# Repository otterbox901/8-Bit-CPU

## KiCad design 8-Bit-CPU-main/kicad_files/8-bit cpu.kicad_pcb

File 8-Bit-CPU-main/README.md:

# 8-Bit CPU

A CPU built from ~97 individual 74HC-series logic ICs. Custom instruction set, microcoded control unit, and a from-scratch ALU with flag logic, laid out on a 4-layer PCB.

## Status: In progress

- [x] Instruction set architecture (11 instructions, custom encoding)
- [x] ALU design — adder/subtractor, bitwise AND/OR, Z/C/N flag generation
- [x] Register file (4 general-purpose registers) and microcoded control-ROM addressing scheme
- [x] PCB component placement — 97 ICs, board outline drawn (173.5 mm × 115.5 mm, 4-layer)
- [x] Microcode ROM generator — Python script producing control-ROM contents from the ISA/microcode design, checked against the control-unit addressing scheme
- [x] Emulator — Python simulator + assembler that executes `microcode_table.csv` directly, with the full ISA exercised by a bundled test program
- [x] Control unit — the schematic's control-ROM addressing, register-file/ALU
      enable logic, and memory control signals are now actually wired
- [x] PCB routing — fully autorouted (4-layer, 755 nets, 0 DRC errors)
- [ ] Power input connector + regulator (not yet designed — see Known Issues)
- [ ] HLT (clock/sequencer halt) — control-ROM signal exists but isn't wired
      to anything yet
- [ ] Burn control ROM onto physical EEPROMs and hardware bring-up

## Overview

| | |
|---|---|
| Data path | 8-bit |
| Registers | 4 general-purpose (R0–R3), plus PC, MAR, IR, and internal ALU staging registers |
| Control unit | Microcoded — control ROM addressed by opcode, execution step, and ALU status flags (no hardwired branch/decision logic) |
| ALU | Add, subtract (two's complement), AND, OR — with Zero, Carry, and Negative flags |
| Memory | Harvard-style — separate address space for program storage (EEPROM) and data storage (SRAM) |
| Clock target | 1–4 MHz |
| Logic family | 74HC/74LS discrete logic |
| IC count | ~97 |
| Board | 4-layer, 1.6 mm, 173.5 mm × 115.5 mm |

## Instruction Set

| Opcode | Mnemonic | Format | Operation |
|---|---|---|---|
| `0000` | `NOP` | — | No operation |
| `0001` | `LOAD Rd, addr` | Address (3 bytes) | Rd ← MEM[addr] |
| `0010` | `STORE Rd, addr` | Address (3 bytes) | MEM[addr] ← Rd |
| `0011` | `ADD Rd, Rs` | Reg-reg (1 byte) | Rd ← Rd + Rs |
| `0100` | `SUB Rd, Rs` | Reg-reg (1 byte) | Rd ← Rd − Rs |
| `0101` | `JMP addr` | Address (3 bytes) | PC ← addr |
| `0110` | `JZ addr` | Address (3 bytes) | PC ← addr if Zero flag set |
| `0111` | `JC addr` | Address (3 bytes) | PC ← addr if Carry flag set |
| `1000` | `MOV Rd, Rs` | Reg-reg (1 byte) | Rd ← Rs |
| `1001` | `AND Rd, Rs` | Reg-reg (1 byte) | Rd ← Rd AND Rs |
| `1010` | `OR Rd, Rs` | Reg-reg (1 byte) | Rd ← Rd OR Rs |
| `1111` | `HLT` | — | Stop the clock |

Opcodes `1011`–`1110` are reserved for future extension (e.g. a stack pointer with `CALL`/`RET`, or additional ALU operations). Currently they fetch and decode as a no-op.

Instructions are encoded as either one byte (reg-reg) or three bytes (address):

| Format | Byte 0 | Byte 1 | Byte 2 |
|---|---|---|---|
| Reg-reg | `[opcode:4][Rd:2][Rs:2]` | — | — |
| Address | `[opcode:4][Rd:2][--:2]` | addr low | addr high |

The 3-bit step counter cycles 0–7 (wrapping); step 0 is always the fetch (`IROM_OUT` + `IR_IN` + `PC_INC`), steps 1–3 execute the operand/operation, and any trailing steps are no-ops. Conditional jumps are resolved entirely by the control ROM's addressing (the flag bits are part of the ROM address), with no separate comparator logic needed.

## Control ROM

The control ROM is generated rather than hand-populated. A Python script (`microcode_rom_gen.py`) walks every `(opcode, step, Z, C)` combination — a 9-bit, 512-word address space, and derives the 20-bit control word for each from the microcode step tables for each instruction. The control word is split across three 28C256 EEPROMs (8 + 8 + 4 bits), and the script emits both a human-readable CSV (`microcode_table.csv`) and three raw 32 KB binary chip images (`rom1.bin`, `rom2.bin`, `rom3.bin`) ready to burn, with unused upper addresses zero-padded to an all-signals-off state.

## Emulator

`emulator.py` is a cycle-accurate Python model of the CPU driven entirely by the generated control ROM. It arbitrates the 8-bit bus, latches registers and flags per the microcode control signals, and assembles + runs programs, so it can be used to develop and verify software before the hardware comes up.

### Usage

```bash
# Generate the control ROM table first (run from ROM/)
python3 microcode_rom_gen.py

# Run the full instruction-set test program (7/7 checks pass)
python3 emulator.py test_program.asm

# Run the bundled default test (no file argument)
python3 emulator.py

# Per-micro-step trace of bus, registers, and control signals
python3 emulator.py test_program.asm --trace-micro

# Quiet mode — suppress trace, show results only
python3 emulator.py -q test_program.asm
```

The built-in two-pass assembler understands the instruction mnemonics, labels, hex/decimal numbers, `.byte` (program ROM data) and `.ram addr, val` (pre-loads the data SRAM) directives. `test_program.asm` exercises every instruction — LOAD, STORE, ADD, SUB, AND, OR, MOV, NOP, JMP, JZ, JC, HLT — and auto-verifies the resulting data RAM contents against expected values.

## Repo Contents

```
8-Bit-CPU/
├── 8-bit cpu.kicad_sch     KiCad schematic (single flat sheet)
├── 8-bit cpu.kicad_pcb     KiCad PCB layout (routed, 0 DRC errors)
├── microcode_rom_gen.py    Control ROM generator (opcode/step/flags → EEPROM images)
├── emulator.py             Microcode-driven CPU emulator + assembler
├── test_program.asm        Full instruction-set test for the emulator
└── README.md
```

## Known Issues

- **No power input connector or regulator.** All 63 live ICs now share a
  single, correctly-named `+5V` net, but nothing in the schematic actually
  sources it — there's no barrel jack/header and no regulator IC modeled.
  This needs to be designed and added before the board can be powered.
- **HLT isn't wired to anything.** The control ROM correctly asserts the
  `HLT` signal per the microcode, but no hardware currently reads it (no
  clock-gating or sequencer-halt logic exists). Without it, a running CPU
  won't literally stop on `HLT` — it'll keep re-fetching the same
  instruction harmlessly forever rather than actually halting.
- **Cosmetic-only DRC/ERC output remains**: ~55 silkscreen text/outline
  overlaps among tightly-packed passives, and footprint-library-name
  mismatches (PCB footprints reference a `fasteda` library not present in
  every environment — the footprint geometry is embedded in the file
  regardless, so this doesn't affect fabrication).
- None of this has been verified against real hardware yet — see Roadmap.

## Roadmap

1. Design and add a power input connector + regulator
2. Wire HLT to a sequencer-halt/clock-gate
3. Burn the generated control ROM contents onto the EEPROMs
4. Bring-up and testing
5. Print and test on physical hardware

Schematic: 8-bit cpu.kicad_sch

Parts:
C1, C2, C3, C4, C5, C6, C7, C8, C9, C10, C11, C12, C13, C14, C15, C16, C17, C18, C19, C20, C21, C22, C23, C24, C25, C26, C27, C28, C29, C30, C31, C32: 100nF; C0805
R1: 10k; R0805
SW1: HX 3X4X2-2P-1.6N TACTILE SWITCH; KEY-SMD_L4.0-W3.0-LS4.9-1; MPN HX 3x4x2-2P-1.6N TACTILE SWITCH; LCSC C49234124
U1, U2, U3, U4, U32, U33, U34, U35, U44, U45, U46, U47, U48, U49, U50, U51, U55, U56: 74HC173D,653; SOP-16_L10.0-W3.9-P1.27-LS6.0-BL; MPN 74HC173D,653; LCSC C546652
U5, U6: CD74HC283M96; SOIC-16_L9.9-W3.9-P1.27-LS6.0-BL; MPN CD74HC283M96; LCSC C543032; not fitted
U7, U8: SN74HC86DR; SOIC-14_L8.7-W3.9-P1.27-LS6.0-BL; MPN SN74HC86DR; LCSC C6763
U9, U10, U11, U12, U38, U39, U40, U41: 74HC153D,653; SOIC-16_L9.9-W3.9-P1.27-LS6.0-BL; MPN 74HC153D,653; LCSC C53334
U13: 74HC245D,653; SOIC-20_L13.0-W7.6-P1.27-LS10.3-BL; MPN 74HC245D,653; LCSC C5625; not fitted
U14, U15: 74HC08D,653; SOIC-14_L8.7-W3.9-P1.27-LS6.0-BL; MPN 74HC08D,653; LCSC C5593
U16, U17, U18, U19: 74HC32D,653; SOIC-14_L8.7-W3.9-P1.27-LS6.0-BL; MPN 74HC32D,653; LCSC C5632
U20: 74HC04D,653; SOIC-14_L8.7-W3.9-P1.27-LS6.0-BL; MPN 74HC04D,653; LCSC C5590
U21: 74HC173D,653; SOP-16_L10.0-W3.9-P1.27-LS6.0-BL; MPN 74HC173D,653; LCSC C546652; not fitted
U22, U23, U24: AT28C256-15SU; SOIC-28_L17.9-W7.6-P1.27-LS10.4-BL; MPN AT28C256-15SU; LCSC C1349121; not fitted
U25, U52, U53, U54: SN74HC161DR; SOIC-16_L9.9-W3.9-P1.27-LS6.0-BL; MPN SN74HC161DR; LCSC C6824
U26, U27, U28, U29, U30: SN74HC161DR; SOIC-16_L9.9-W3.9-P1.27-LS6.0-BL; MPN SN74HC161DR; LCSC C6824; not fitted
U31: AT28C64B-15PU; DIP-28_L37.0-W13.8-P2.54-LS15.8-BL; MPN AT28C64B-15PU; LCSC C41982; not fitted
U36, U37: CD74HC283M96; SOIC-16_L9.9-W3.9-P1.27-LS6.0-BL; MPN CD74HC283M96; LCSC C543032
U42: 74HC245D,653; SOIC-20_L13.0-W7.6-P1.27-LS10.3-BL; MPN 74HC245D,653; LCSC C5625
U43: 74HC139D,653; SOIC-16_L9.9-W3.9-P1.27-LS6.0-BL; MPN 74HC139D,653; LCSC C5603
U57, U58, U59: AT28C256-15SU; SOIC-28_L17.9-W7.6-P1.27-LS10.4-BL; MPN AT28C256-15SU; LCSC C1349121
U60: AT28C64B-15PU; DIP-28_L37.0-W13.8-P2.54-LS15.8-BL; MPN AT28C64B-15PU; LCSC C41982
U61: HM6116LP-4; DIP-24_W15.24mm_P2.54mm; MPN HM6116LP-4
U62: OT70501MJBA4SL; OSC-SMD_4P-L7.0-W5.0-BL-2; MPN OT70501MJBA4SL; LCSC C2831414
U63: SN74HC14DR; SOIC-14_L8.7-W3.9-P1.27-LS6.0-BL; MPN SN74HC14DR; LCSC C6820

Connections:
+5V: C1.1, C2.1, C3.1, C4.1, C5.1, C6.1, C7.1, C8.1, C9.1, C10.1, C11.1, C12.1, C13.1, C14.1, C15.1, C16.1, C17.1, C18.1, C19.1, C20.1, C21.1, C22.1, C23.1, C24.1, C25.1, C26.1, C27.1, C28.1, C29.1, C30.1, C31.1, C32.1, R1.1, U1.16 (VCC), U2.16 (VCC), U3.16 (VCC), U4.16 (VCC), U5.16 (VCC), U6.16 (VCC), U7.14 (VCC), U8.14 (VCC), U9.16 (VCC), U10.6 (1I0), U10.10 (2I0), U10.16 (VCC), U11.6 (1I0), U11.10 (2I0), U11.16 (VCC), U12.6 (1I0), U12.10 (2I0), U12.16 (VCC), U13.20 (VCC), U14.14 (VCC), U15.14 (VCC), U16.14 (VCC), U17.14 (VCC), U18.14 (VCC), U19.14 (VCC), U20.14 (VCC), U21.16 (VCC), U22.28 (VCC), U23.27 (~WE), U23.28 (VCC), U24.28 (VCC), U25.7 (ENP), U25.9 (~LOAD), U25.10 (ENT), U25.16 (VCC), U26.16 (VCC), U27.16 (VCC), U28.16 (VCC), U29.16 (VCC), U30.16 (VCC), U31.28 (VCC), U32.16 (VCC), U33.16 (VCC), U34.16 (VCC), U35.16 (VCC), U36.16 (VCC), U37.16 (VCC), U38.16 (VCC), U39.16 (VCC), U40.16 (VCC), U41.16 (VCC), U42.20 (VCC), U43.16 (VCC), U44.16 (VCC), U45.16 (VCC), U46.16 (VCC), U47.16 (VCC), U48.16 (VCC), U49.16 (VCC), U50.16 (VCC), U51.16 (VCC), U52.16 (VCC), U53.16 (VCC), U54.16 (VCC), U55.16 (VCC), U56.16 (VCC), U57.27 (~WE), U57.28 (VCC), U58.27 (~WE), U58.28 (VCC), U59.27 (~WE), U59.28 (VCC), U60.27 (~WE), U60.28 (VCC), U61.24 (VCC), U62.1 (Tri-state), U62.4 (VDD), U63.14 (VCC)
A0: U23.10 (A0), U31.10 (A0)
A1: U23.9 (A1), U31.9 (A1)
A2: U23.8 (A2), U31.8 (A2)
A3: U23.7 (A3), U31.7 (A3)
A4: U23.6 (A4), U31.6 (A4)
A5: U23.5 (A5), U31.5 (A5)
A6: U23.4 (A6), U31.4 (A6)
A7: U23.3 (A7), U31.3 (A7)
A8: U23.25 (A8), U31.25 (A8)
A9: U23.24 (A9), U31.24 (A9)
A10: U23.21 (A10), U31.21 (A10)
A11: U23.23 (A11), U31.23 (A11)
A12: U23.2 (A12), U31.2 (A12)
A13_ADDR: U23.26 (A13)
A14: U23.1 (A14)
ALU_A0: U14.1 (1A), U16.1 (1A), U32.3 (Q0), U36.5 (A0)
ALU_A0_2: U5.5 (A0)
ALU_A1: U14.4 (2A), U16.4 (2A), U32.4 (Q1), U36.3 (A1)
ALU_A1_2: U5.3 (A1)
ALU_A2: U14.9 (3A), U16.9 (3A), U32.5 (Q2), U36.14 (A2)
ALU_A2_2: U5.14 (A2)
ALU_A3: U14.12 (4A), U16.12 (4A), U32.6 (Q3), U36.12 (A3)
ALU_A3_2: U5.12 (A3)
ALU_A4: U15.1 (1A), U17.1 (1A), U34.3 (Q0), U37.5 (A0)
ALU_A4_2: U6.5 (A0)
ALU_A5: U15.4 (2A), U17.4 (2A), U34.4 (Q1), U37.14 (A2)
ALU_A5_2: U6.14 (A2)
ALU_A6: U15.9 (3A), U17.9 (3A), U34.5 (Q2), U37.3 (A1)
ALU_A6_2: U6.3 (A1)
ALU_A7: U15.12 (4A), U17.12 (4A), U34.6 (Q3), U37.12 (A3)
ALU_A7_2: U6.12 (A3)
ALU_AND0: U14.3 (1Y), U38.5 (1I1)
ALU_AND1: U14.6 (2Y), U38.11 (2I1)
ALU_AND2: U14.8 (3Y), U39.5 (1I1)
ALU_AND3: U14.11 (4Y), U39.11 (2I1)
ALU_AND4: U15.3 (1Y), U40.5 (1I1)
ALU_AND5: U15.6 (2Y), U40.11 (2I1)
ALU_AND6: U15.8 (3Y), U41.5 (1I1)
ALU_AND7: U15.11 (4Y), U41.11 (2I1)
ALU_B0: U7.3 (1Y), U14.2 (1B), U16.2 (1B), U36.6 (B0), U38.3 (1I3)
ALU_B0_2: U5.6 (B0)
ALU_B1: U7.6 (2Y), U14.5 (2B), U16.5 (2B), U36.2 (B1), U38.13 (2I3)
ALU_B1_2: U5.2 (B1)
ALU_B2: U7.8 (3Y), U14.10 (3B), U16.10 (3B), U36.15 (B2), U39.3 (1I3)
ALU_B2_2: U5.15 (B2)
ALU_B3: U7.11 (4Y), U14.13 (4B), U16.13 (4B), U36.11 (B3), U39.13 (2I3)
ALU_B3_2: U5.11 (B3)
ALU_B4: U8.3 (1Y), U15.2 (1B), U17.2 (1B), U37.6 (B0), U40.3 (1I3)
ALU_B4_2: U6.6 (B0)
ALU_B5: U8.6 (2Y), U15.5 (2B), U17.5 (2B), U37.15 (B2), U40.13 (2I3)
ALU_B5_2: U6.15 (B2)
ALU_B6: U8.8 (3Y), U15.10 (3B), U17.10 (3B), U37.2 (B1), U41.3 (1I3)
ALU_B6_2: U6.2 (B1)
ALU_B7: U8.11 (4Y), U15.13 (4B), U17.13 (4B), U37.11 (B3), U41.13 (2I3)
ALU_B7_2: U6.11 (B3)
ALU_B_RAW0: U7.1 (1A), U33.3 (Q0)
ALU_B_RAW1: U7.4 (2A), U33.4 (Q1)
ALU_B_RAW2: U7.9 (3A), U33.5 (Q2)
ALU_B_RAW3: U7.12 (4A), U33.6 (Q3)
ALU_B_RAW4: U8.1 (1A), U35.3 (Q0)
ALU_B_RAW5: U8.4 (2A), U35.4 (Q1)
ALU_B_RAW6: U8.9 (3A), U35.5 (Q2)
ALU_B_RAW7: U8.12 (4A), U35.6 (Q3)
ALU_CARRY_MID: U36.9 (COUT), U37.7 (CIN)
ALU_MUX_OUT0: U18.1 (1A), U38.7 (1Y), U42.18 (B0)
ALU_MUX_OUT1: U18.2 (1B), U38.9 (2Y), U42.17 (B1)
ALU_MUX_OUT2: U18.4 (2A), U39.7 (1Y), U42.16 (B2)
ALU_MUX_OUT3: U18.5 (2B), U39.9 (2Y), U42.15 (B3)
ALU_MUX_OUT4: U18.9 (3A), U40.7 (1Y), U42.14 (B4)
ALU_MUX_OUT5: U18.10 (3B), U40.9 (2Y), U42.13 (B5)
ALU_MUX_OUT6: U18.12 (4A), U41.7 (1Y), U42.12 (B6)
ALU_MUX_OUT7: U18.13 (4B), U41.9 (2Y), U42.11 (B7)
ALU_OR0: U16.3 (1Y), U38.4 (1I2)
ALU_OR1: U16.6 (2Y), U38.12 (2I2)
ALU_OR2: U16.8 (3Y), U39.4 (1I2)
ALU_OR3: U16.11 (4Y), U39.12 (2I2)
ALU_OR4: U17.3 (1Y), U40.4 (1I2)
ALU_OR5: U17.6 (2Y), U40.12 (2I2)
ALU_OR6: U17.8 (3Y), U41.4 (1I2)
ALU_OR7: U17.11 (4Y), U41.12 (2I2)
ALU_S0: U36.4 (S0), U38.6 (1I0)
ALU_S1: U36.1 (S1), U38.10 (2I0)
ALU_S2: U36.13 (S2), U39.6 (1I0)
ALU_S3: U36.10 (S3), U39.10 (2I0)
ALU_S4: U37.4 (S0), U40.6 (1I0)
ALU_S5: U37.1 (S1), U40.10 (2I0)
ALU_S6: U37.13 (S2), U41.6 (1I0)
ALU_S7: U37.10 (S3), U41.10 (2I0)
ALU_SEL0: U38.14 (S0), U39.14 (S0), U40.14 (S0), U41.14 (S0), U58.17 (I/O5)
ALU_SEL1: U38.2 (S1), U39.2 (S1), U40.2 (S1), U41.2 (S1), U58.18 (I/O6)
A_IN: U32.9 (#E1), U32.10 (#E2), U34.9 (#E1), U34.10 (#E2), U58.15 (I/O3)
C: U4.4 (Q1), U57.10 (A0), U58.10 (A0), U59.10 (A0)
CIN: U5.9 (COUT), U6.7 (CIN)
CLK: U1.7 (CP), U2.7 (CP), U3.7 (CP), U4.7 (CP), U25.2 (CLK), U32.7 (CP), U33.7 (CP), U34.7 (CP), U35.7 (CP), U44.7 (CP), U45.7 (CP), U46.7 (CP), U47.7 (CP), U48.7 (CP), U49.7 (CP), U50.7 (CP), U51.7 (CP), U52.2 (CLK), U53.2 (CLK), U54.2 (CLK), U55.7 (CP), U56.7 (CP), U62.3 (OUTPUT)
CLK_2: U21.7 (CP), U26.2 (CLK), U27.2 (CLK), U28.2 (CLK), U29.2 (CLK), U30.2 (CLK)
C_COMPUTED: U4.13 (D1), U37.9 (COUT)
D0: U23.11 (I/O0), U31.11 (IO0)
D1: U23.12 (I/O1), U31.12 (IO1)
D2: U23.13 (I/O2), U31.13 (IO2)
D3: U23.15 (I/O3), U31.15 (IO3)
D4: U23.16 (I/O4), U31.16 (IO4), U59.16 (I/O4)
D5: U23.17 (I/O5), U31.17 (IO5), U59.17 (I/O5)
D6: U23.18 (I/O6), U31.18 (IO6), U59.18 (I/O6)
D7: U23.19 (I/O7), U31.19 (IO7), U59.19 (I/O7)
DBUS0: U1.14 (D0), U3.14 (D0), U32.14 (D0), U33.14 (D0), U42.2 (A0), U44.3 (Q0), U44.14 (D0), U46.3 (Q0), U46.14 (D0), U48.3 (Q0), U48.14 (D0), U50.3 (Q0), U50.14 (D0), U55.14 (D0), U60.11 (IO0), U61.9 (I/O0)
DBUS0_2: U13.2 (A0), U21.14 (D0)
DBUS1: U1.13 (D1), U3.13 (D1), U32.13 (D1), U33.13 (D1), U42.3 (A1), U44.4 (Q1), U44.13 (D1), U46.4 (Q1), U46.13 (D1), U48.4 (Q1), U48.13 (D1), U50.4 (Q1), U50.13 (D1), U55.13 (D1), U60.12 (IO1), U61.10 (I/O1)
DBUS1_2: U13.3 (A1), U21.13 (D1)
DBUS2: U1.12 (D2), U3.12 (D2), U32.12 (D2), U33.12 (D2), U42.4 (A2), U44.5 (Q2), U44.12 (D2), U46.5 (Q2), U46.12 (D2), U48.5 (Q2), U48.12 (D2), U50.5 (Q2), U50.12 (D2), U55.12 (D2), U60.13 (IO2), U61.11 (I/O2)
DBUS2_2: U13.4 (A2), U21.12 (D2)
DBUS3: U1.11 (D3), U3.11 (D3), U32.11 (D3), U33.11 (D3), U42.5 (A3), U44.6 (Q3), U44.11 (D3), U46.6 (Q3), U46.11 (D3), U48.6 (Q3), U48.11 (D3), U50.6 (Q3), U50.11 (D3), U55.11 (D3), U60.15 (IO3), U61.13 (I/O3)
DBUS3_2: U13.5 (A3), U21.11 (D3)
DBUS4: U2.14 (D0), U34.14 (D0), U35.14 (D0), U42.6 (A4), U45.3 (Q0), U45.14 (D0), U47.3 (Q0), U47.14 (D0), U49.3 (Q0), U49.14 (D0), U51.3 (Q0), U51.14 (D0), U56.14 (D0), U60.16 (IO4), U61.14 (I/O4)
DBUS5: U2.13 (D1), U34.13 (D1), U35.13 (D1), U42.7 (A5), U45.4 (Q1), U45.13 (D1), U47.4 (Q1), U47.13 (D1), U49.4 (Q1), U49.13 (D1), U51.4 (Q1), U51.13 (D1), U56.13 (D1), U60.17 (IO5), U61.15 (I/O5)
DBUS6: U2.12 (D2), U34.12 (D2), U35.12 (D2), U42.8 (A6), U45.5 (Q2), U45.12 (D2), U47.5 (Q2), U47.12 (D2), U49.5 (Q2), U49.12 (D2), U51.5 (Q2), U51.12 (D2), U56.12 (D2), U60.18 (IO6), U61.16 (I/O6)
DBUS7: U2.11 (D3), U34.11 (D3), U35.11 (D3), U42.9 (A7), U45.6 (Q3), U45.11 (D3), U47.6 (Q3), U47.11 (D3), U49.6 (Q3), U49.11 (D3), U51.6 (Q3), U51.11 (D3), U56.11 (D3), U60.19 (IO7), U61.17 (I/O7)
EO: U12.14 (S0), U59.11 (I/O0)
EO_N: U12.7 (1Y), U12.9 (2Y), U42.19 (~OE)
FI_C: U19.13 (4B), U59.13 (I/O2)
FI_LATCH_N: U4.9 (#E1), U4.10 (#E2), U11.7 (1Y), U11.9 (2Y)
FI_OR: U11.14 (S0), U19.11 (4Y)
FI_ZN: U19.12 (4A), U59.12 (I/O1)
HLT: U59.15 (I/O3)
IROM_OUT: U20.1 (1A), U57.11 (I/O0)
IROM_OUT_N: U20.2 (1Y), U60.22 (~OE)
IR_IN: U55.9 (#E1), U55.10 (#E2), U56.9 (#E1), U56.10 (#E2), U57.15 (I/O3)
IR_RD0: U9.6 (1I0), U55.5 (Q2)
IR_RD1: U9.10 (2I0), U55.6 (Q3)
IR_RS0: U9.5 (1I1), U55.3 (Q0)
IR_RS1: U9.11 (2I1), U55.4 (Q1)
MARH0: U3.3 (Q0), U54.3 (A), U61.23 (A8)
MARH1: U3.4 (Q1), U54.4 (B), U61.22 (A9)
MARH2: U3.5 (Q2), U54.5 (C), U61.19 (A10)
MARH3: U3.6 (Q3), U54.6 (D)
MARL0: U1.3 (Q0), U52.3 (A), U61.8 (A0)
MARL1: U1.4 (Q1), U52.4 (B), U61.7 (A1)
MARL2: U1.5 (Q2), U52.5 (C), U61.6 (A2)
MARL3: U1.6 (Q3), U52.6 (D), U61.5 (A3)
MARL4: U2.3 (Q0), U53.3 (A), U61.4 (A4)
MARL5: U2.4 (Q1), U53.4 (B), U61.3 (A5)
MARL6: U2.5 (Q2), U53.5 (C), U61.2 (A6)
MARL7: U2.6 (Q3), U53.6 (D), U61.1 (A7)
MAR_HIGH_IN: U3.9 (#E1), U3.10 (#E2), U57.17 (I/O5)
MAR_LOW_IN: U1.9 (#E1), U1.10 (#E2), U2.9 (#E1), U2.10 (#E2), U57.16 (I/O4)
unnamed: SW1.1, U63.1 (1A)
OE: U23.22 (~OE)
OPCODE0: U56.3 (Q0), U57.5 (A5), U58.5 (A5), U59.5 (A5)
OPCODE1: U56.4 (Q1), U57.4 (A6), U58.4 (A6), U59.4 (A6)
OPCODE2: U56.5 (Q2), U57.3 (A7), U58.3 (A7), U59.3 (A7)
OPCODE3: U56.6 (Q3), U57.25 (A8), U58.25 (A8), U59.25 (A8)
PC0: U52.14 (QA), U60.10 (A0)
PC1: U52.13 (QB), U60.9 (A1)
PC2: U52.12 (QC), U60.8 (A2)
PC3: U52.11 (QD), U60.7 (A3)
PC4: U53.14 (QA), U60.6 (A4)
PC5: U53.13 (QB), U60.5 (A5)
PC6: U53.12 (QC), U60.4 (A6)
PC7: U53.11 (QD), U60.3 (A7)
PC8: U54.14 (QA), U60.25 (A8)
PC9: U54.13 (QB), U60.24 (A9)
PC10: U60.21 (A10)
PC11: U60.23 (A11)
PC_CARRY0: U52.15 (RCO), U53.7 (ENP), U53.10 (ENT)
PC_CARRY1: U53.15 (RCO), U54.7 (ENP), U54.10 (ENT)
PC_INC: U52.7 (ENP), U52.10 (ENT), U57.18 (I/O6)
PC_LOAD: U20.13 (6A), U57.19 (I/O7)
PC_LOAD_N: U20.12 (6Y), U52.9 (~LOAD), U53.9 (~LOAD), U54.9 (~LOAD)
RAM_IN: U20.5 (3A), U57.13 (I/O2)
RAM_IN_N: U20.6 (3Y), U61.21 (WE)
RAM_OUT: U20.3 (2A), U57.12 (I/O1)
RAM_OUT_N: U20.4 (2Y), U61.20 (OE)
REGSEL_Y0: U43.4 (~1Y0), U44.1 (#OE1), U44.9 (#E1), U45.1 (#OE1), U45.9 (#E1)
REGSEL_Y1: U43.5 (~1Y1), U46.1 (#OE1), U46.9 (#E1), U47.1 (#OE1), U47.9 (#E1)
REGSEL_Y2: U43.6 (~1Y2), U48.1 (#OE1), U48.9 (#E1), U49.1 (#OE1), U49.9 (#E1)
REGSEL_Y3: U43.7 (~1Y3), U50.1 (#OE1), U50.9 (#E1), U51.1 (#OE1), U51.9 (#E1)
REG_IN: U20.9 (4A), U58.12 (I/O1)
REG_IN_N: U20.8 (4Y), U44.10 (#E2), U45.10 (#E2), U46.10 (#E2), U47.10 (#E2), U48.10 (#E2), U49.10 (#E2), U50.10 (#E2), U51.10 (#E2)
REG_OUT: U20.11 (5A), U58.13 (I/O2)
REG_OUT_N: U20.10 (5Y), U44.2 (#OE), U45.2 (#OE), U46.2 (#OE), U47.2 (#OE), U48.2 (#OE), U49.2 (#OE), U50.2 (#OE), U51.2 (#OE)
REG_SEL0: U9.7 (1Y), U43.2 (1A0)
REG_SEL1: U9.9 (2Y), U43.3 (1A1)
RESET_N: U25.1 (~CLR), U52.1 (~CLR), U53.1 (~CLR), U54.1 (~CLR), U63.2 (1Y)
ROM_CE: U31.20 (~CE)
ROM_CS: U23.20 (~CE)
ROM_OE: U31.22 (~OE)
ROM_WE: U31.27 (~WE)
RS_SEL: U9.14 (S0), U58.11 (I/O0)
STEP0: U25.14 (QA), U57.8 (A2), U58.8 (A2), U59.8 (A2)
STEP1: U25.13 (QB), U57.7 (A3), U58.7 (A3), U59.7 (A3)
STEP2: U25.12 (QC), U57.6 (A4), U58.6 (A4), U59.6 (A4)
SU: U7.2 (1B), U7.5 (2B), U7.10 (3B), U7.13 (4B), U8.2 (1B), U8.5 (2B), U8.10 (3B), U8.13 (4B), U36.7 (CIN), U58.19 (I/O7)
TEMP_IN: U33.9 (#E1), U33.10 (#E2), U35.9 (#E1), U35.10 (#E2), U58.16 (I/O4)
Z: U4.3 (Q0), U57.9 (A1), U58.9 (A1), U59.9 (A1)
ZT_G1: U18.3 (1Y), U19.1 (1A)
ZT_G2: U18.6 (2Y), U19.2 (1B)
ZT_G3: U18.8 (3Y), U19.4 (2A)
ZT_G4: U18.11 (4Y), U19.5 (2B)
ZT_G5: U19.3 (1Y), U19.9 (3A)
ZT_G6: U19.6 (2Y), U19.10 (3B)
ZT_G7: U10.14 (S0), U19.8 (3Y)
Z_COMPUTED: U4.14 (D0), U10.7 (1Y), U10.9 (2Y)

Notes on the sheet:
Register File (R0-R3)
PROTOFLOW_REGION:eyJpZCI6IjU4ZTk1ZGUwLWQ1NzItNDgwZS1iOGE4LTMwOGQ0NjZiYzUxMCIsIm5hbWUiOiJNaWNyb2NvZGVkIENvbnRyb2wgVW5pdCIsIngxIjoyODk5LjQxNTk5OTk5OTk5OTcsInkxIjo2OTUyLjc3OTk5OTk5OTk5OSwieDIiOjM1NzAuNjA0LCJ5MiI6NzUyMC42MTk5OTk5OTk5OTksImNvbG9yIjo0Mjg1NTA3ODA0LCJkZXNjcmlwdGlvbiI6bnVsbCwiY29tcG9uZW50SW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
ALU & Accumulator
PC & MAR
PROTOFLOW_REGION:eyJpZCI6ImQwOGRlMzg5LTczMzYtNDk4Yy04ODE5LWVmMjRlN2U5MTFmZiIsIm5hbWUiOiJQQyAmIE1BUiIsIngxIjo2ODEuOTQ4MDQ1NDA4OTc3NiwieTEiOjU0ODguOTY3ODgyMjI3OTUzLCJ4MiI6MTY0My41OTg2NTkwOTg1MDM1LCJ5MiI6NTkwMi4xOTI3MDY2MzIyODIsImNvbG9yIjo0Mjg1NTA3ODA0LCJkZXNjcmlwdGlvbiI6bnVsbCwiY29tcG9uZW50SWRzIjpbIj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
Microcoded Control Unit
PROTOFLOW_REGION:eyJpZCI6Ijc0NTk5OWZjLThkMjAtNDZjZi1iOTllLWVmZjEyNDk2OTU4YyIsIm5hbWUiOiJSZWdpc3RlciBGaWxlIChSMC1SMykiLCJ4MSI6Mjg2Ny44NiwieTEiOjM2MzMuMCwieDIiOjM4NDguODM5OTk5OTk5OTk5NywieTIiOjQzMjUuMjk5OTk5OTk5OTk5LCJjb2xvciI6NDI4NTUwNzgwNCwiZGVzY3JpcHRpb24iOm51bGwsImNvbXBvbmVudElkcyI6WyI3NDlmZTUxMi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
PROTOFLOW_REGION:eyJpZCI6IjVkNGIwZmM1LTFhMTAtNDM5ZS04NDNmLWZhNTM1OTEyMjRjNSIsIm5hbWUiOiJJbnN0cnVjdGlvbiBSZWdpc3RlciIsIngxIjo2ODg3LjQ2MDA2NzgzOTc5NjUsInkxIjo1NDI0LjY0MDI1NDM5OTIzNywieDIiOjc1NTYuOTM5NTkyOTYxMjI0LCJ5MiI6NTg2My45NTk5NTc2MDAxMjcsImNvbG9yIjo0Mjg1NTA3ODA0LCJkZXNjcmlwdGlvbiI6bnVsbCwiY29tcG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
Harvard Memory (ROM/RAM)
PROTOFLOW_REGION:eyJpZCI6IjgxODk1M2NkLTIwNDctNGZhOS04OWJjLWY2ZTA4OGU5NjlkOCIsIm5hbWUiOiJJbnN0cnVjdGlvbiBSZWdpc3RlciIsIngxIjo4ODQzLjcwMDA2NzgzOTc5NiwieTEiOjUxMjcuNDYwMjU0Mzk5MjM3LCJ4MiI6OTU0Mi4yOTk1OTI5NjEyMjMsInkyIjo3NjQ3LjAzOTk1NzYwMDEyNywiY29sb3IiOjQyODU1MDc4MDQsImRlc2NyaXB0aW9uIjpudWxsLCJjb21wb2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
Instruction Register
PROTOFLOW_REGION:eyJpZCI6IjUwMTk2OGM1LWJhNDQtNGM0NC1iZjc2LTNjNGEwOTgwY2MwZCIsIm5hbWUiOiJBTFUgJiBBY2N1bXVsYXRvciIsIngxIjoxMzk5LjQyLCJ5MSI6MTIwNC43NiwieDIiOjM1OTEuNjgwMDAwMDAwMDAwMywieTIiOjMwNzAuNTQsImNvbG9yIjo0Mjg1NTA3ODA0LCJkZXNjcmlwdGlvbiI6bnVsbCwiY29tcG9uZW50SWRzIjpbImFiYWQ5NWEwLWFmOTQtNGUxOS1hNG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
PROTOFLOW_REGION:eyJpZCI6ImE2YzI4Y2E5LTZkZjEtNDk1NS1iODRlLTMyMjFmNzJhYzUxMSIsIm5hbWUiOiJBTFUgJiBBY2N1bXVsYXRvciIsIngxIjoxMDg5NS40NDIxNTY2MTAzMjMsInkxIjo3NDUuNTA4NzM3MDgwMDEwMiwieDIiOjExNzMwLjAwOTMxODQ2NDkyNywieTIiOjExNjEuNjQ4NTQzODE5OTk4NCwiY29sb3IiOjQyODU1MDc4MDQsImRlc2NyaXB0aW9uIjpudWxsLCJjb21wb2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
PROTOFLOW_REGION:eyJpZCI6ImY1NGE1ZjVkLTI3MzctNDcwYS1hYWE1LWYzOGVjYjY1ZTQxNiIsIm5hbWUiOiJBTFUgJiBBY2N1bXVsYXRvciIsIngxIjo1Nzc4LjQzOTk5OTk5OTk5OSwieTEiOjEzODIuNTYsIngyIjo3NDE2Ljg2MDAwMDAwMDAwMSwieTIiOjMyNDguMzM5OTk5OTk5OTk5LCJjb2xvciI6NDI4NTUwNzgwNCwiZGVzY3JpcHRpb24iOm51bGwsImNvbXBvbmVudElkcyI6WyJlMT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
PROTOFLOW_REGION:eyJpZCI6IjY5YTFmMGFkLWIxYjItNDAzNy1hN2QzLTY4MjFiODA4MDY5NiIsIm5hbWUiOiJBTFUgJiBBY2N1bXVsYXRvciIsIngxIjo5MjYxLjQ5NiwieTEiOjc5OC4zNjAwMDAwMDAwMDAxLCJ4MiI6OTk0OC4yMjM5OTk5OTk5OTgsInkyIjoxMTUyLjgzOTk5OTk5OTk5OTcsImNvbG9yIjo0Mjg1NTA3ODA0LCJkZXNjcmlwdGlvbiI6bnVsbCwiY29tcG9uZW50SWRzIjpbIj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
PROTOFLOW_REGION:eyJpZCI6ImM1ZWZlYzMwLTgwMmQtNDFiYy1iMjNmLTBmMzZiY2YyMzBiZiIsIm5hbWUiOiJQQyAmIE1BUiIsIngxIjo5ODEuNjkxOTk5OTk5OTk5MSwieTEiOjQzMDguMTYsIngyIjoxMjMwMy4wOTk5OTk5OTk5OTksInkyIjo3ODYzLjAzOTk5OTk5OTk5OSwiY29sb3IiOjQyODU1MDc4MDQsImRlc2NyaXB0aW9uIjpudWxsLCJjb21wb25lbnRJZHMiOlsiOTM2Y2YyNDMtMT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
PROTOFLOW_REGION:eyJpZCI6ImYzOGFlNmUzLTgwYzktNDg3Ny04YTE1LTFjMGM4ZDU0ODU0YSIsIm5hbWUiOiJBTFUgJiBBY2N1bXVsYXRvciIsIngxIjoxNjY1LjAzOTk5OTk5OTk5OTUsInkxIjozMDgyLjMwODczNzA4MDAwOTUsIngyIjo0MDQyLjY1OTk5OTk5OTk5OTQsInkyIjozOTQyLjk0ODU0MzgxOTk5NywiY29sb3IiOjQyODU1MDc4MDQsImRlc2NyaXB0aW9uIjpudWxsLCJjb21wb2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
PROTOFLOW_REGION:eyJpZCI6ImYwNzBlMWE5LWNlMWYtNGMyOC04OGFiLTJhNWIyNzhlZmM4NiIsIm5hbWUiOiJSZWdpc3RlciBGaWxlIChSMC1SMykiLCJ4MSI6NzIwNy4yNTU5OTk5OTk5OTksInkxIjoyMjk2Ljk2LCJ4MiI6ODMwNS4xNjQsInkyIjozMDk1LjkzOTk5OTk5OTk5ODcsImNvbG9yIjo0Mjg1NTA3ODA0LCJkZXNjcmlwdGlvbiI6bnVsbCwiY29tcG9uZW50SWRzIjpbIjg1MTRiMT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
PROTOFLOW_REGION:eyJpZCI6ImQwNmEyMDI4LTdiNDgtNDUxNi1hNGFiLTVmMzEzM2Y0Y2ExNSIsIm5hbWUiOiJBTFUgJiBBY2N1bXVsYXRvciIsIngxIjozNzE2LjgxOTk5OTk5OTk5OTcsInkxIjoxMjA0Ljc2LCJ4MiI6NTc3OC4xNzk5OTk5OTk5OTg1LCJ5MiI6MzA3MC41NCwiY29sb3IiOjQyODU1MDc4MDQsImRlc2NyaXB0aW9uIjpudWxsLCJjb21wb25lbnRJZHMiOlsiZjUyYjZhMWUtMj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
PROTOFLOW_REGION:eyJpZCI6IjA1MzM3YmE4LTVmNjItNGNmYi04MjliLWY0OWIwY2YxMTU5MyIsIm5hbWUiOiJSZWdpc3RlciBGaWxlIChSMC1SMykiLCJ4MSI6MTEwMDIuMjYwMDY3ODM5Nzk4LCJ5MSI6MjI4Ny43NDAyNTQzOTkyMzY2LCJ4MiI6MTE2NzEuNzM5NTkyOTYxMjIxLCJ5MiI6MjcyNy4wNTk5NTc2MDAxMjcsImNvbG9yIjo0Mjg1NTA3ODA0LCJkZXNjcmlwdGlvbiI6bnVsbCwiY2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
PROTOFLOW_REGION:eyJpZCI6ImFlMDAwMWJlLTI4MTItNDBlZC1iNWNmLWU3NWY5Y2IzMGYyNCIsIm5hbWUiOiJNaWNyb2NvZGVkIENvbnRyb2wgVW5pdCIsIngxIjoxMDg0OS42MTYsInkxIjo1MzkwLjY3OTk5OTk5OTk5OSwieDIiOjExNTIwLjgwMzk5OTk5OTk5OCwieTIiOjU5NTguNTE5OTk5OTk5OTk5NSwiY29sb3IiOjQyODU1MDc4MDQsImRlc2NyaXB0aW9uIjpudWxsLCJjb21wb25lbn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
PROTOFLOW_REGION:eyJpZCI6Ijg3YWQxMjgyLWNjYzAtNDIwYS04NDJiLTIxMDcwOGU0NDUxNiIsIm5hbWUiOiJSZWdpc3RlciBGaWxlIChSMC1SMykiLCJ4MSI6NDA3NC44Nzk5OTk5OTk5OTk3LCJ5MSI6MzU0MS41NTk5OTk5OTk5OTk1LCJ4MiI6ODM1Mi43MiwieTIiOjU0MDcuMzQsImNvbG9yIjo0Mjg1NTA3ODA0LCJkZXNjcmlwdGlvbiI6bnVsbCwiY29tcG9uZW50SWRzIjpbImE0ZTZmZj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
PROTOFLOW_REGION:eyJpZCI6Ijg3YjU1NjIxLWJhODgtNDBlYy05MWQyLWRlYTY3ZmE5ZTg0ZCIsIm5hbWUiOiJSZWdpc3RlciBGaWxlIChSMC1SMykiLCJ4MSI6ODg2OC42NjAwNjc4Mzk3OTUsInkxIjozODQ5Ljg0MDI1NDM5OTIzNiwieDIiOjk1MzguMTM5NTkyOTYxMjIzLCJ5MiI6NDI4OS4xNTk5NTc2MDAxMjYsImNvbG9yIjo0Mjg1NTA3ODA0LCJkZXNjcmlwdGlvbiI6bnVsbCwiY29tcG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
PROTOFLOW_REGION:eyJpZCI6ImUzOTU4MWMxLTA1MGMtNDlmOC05MzM5LTkwOTQyYzM4MGRhZSIsIm5hbWUiOiJBTFUgJiBBY2N1bXVsYXRvciIsIngxIjo1NTguNDYyOTEyMzYwMDAzMiwieTEiOjMwODIuMzA4NzM3MDgwMDEwNCwieDIiOjE1MjUuNDIyNTI1ODM5OTgsInkyIjozOTQyLjk0ODU0MzgxOTk5OCwiY29sb3IiOjQyODU1MDc4MDQsImRlc2NyaXB0aW9uIjpudWxsLCJjb21wb25lbn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
PROTOFLOW_REGION:eyJpZCI6IjI0Yjk0NjM3LTllN2EtNGIxYy1hMWNlLWJjOTQzMmY4ODQ5MyIsIm5hbWUiOiJBTFUgJiBBY2N1bXVsYXRvciIsIngxIjo3MzQ2Ljk1NiwieTEiOjQ5NS43NjAwNDIzOTk4NzI3LCJ4MiI6ODI2Ny4wNjM5OTk5OTk5OTgsInkyIjoxMjc5LjMzOTc0NTYwMDc2MywiY29sb3IiOjQyODU1MDc4MDQsImRlc2NyaXB0aW9uIjpudWxsLCJjb21wb25lbnRJZHMiOlsiMG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
PROTOFLOW_REGION:eyJpZCI6ImMxYjY3ZDc2LTdhZTgtNGE0MC1hYzdjLTE3NTYxNzU1NDQxNyIsIm5hbWUiOiJSZWdpc3RlciBGaWxlIChSMC1SMykiLCJ4MSI6OTMwMC40NjAwNjc4Mzk3OTYsInkxIjoyMjg3Ljc0MDI1NDM5OTIzNjYsIngyIjo5OTY5LjkzOTU5Mjk2MTIyLCJ5MiI6MjcyNy4wNTk5NTc2MDAxMjcsImNvbG9yIjo0Mjg1NTA3ODA0LCJkZXNjcmlwdGlvbiI6bnVsbCwiY29tcG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
PROTOFLOW_REGION:eyJpZCI6ImEyYzkzMjg1LTRiMDUtNGUwOS04NmU0LTRiZjkwMGI0OWM0ZSIsIm5hbWUiOiJNaWNyb2NvZGVkIENvbnRyb2wgVW5pdCIsIngxIjo5MDUuNTE1OTk5OTk5OTk5OCwieTEiOjY5NTIuNzc5OTk5OTk5OTk5LCJ4MiI6MTU3Ni43MDQsInkyIjo3NTIwLjYxOTk5OTk5OTk5OSwiY29sb3IiOjQyODU1MDc4MDQsImRlc2NyaXB0aW9uIjpudWxsLCJjb21wb25lbnRJZH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
PROTOFLOW_REGION:eyJpZCI6ImQ0OWIxNWI2LWQ5OGUtNGYyYS1iNWJkLTdmMWU4NTJiYWIyYyIsIm5hbWUiOiJSZWdpc3RlciBGaWxlIChSMC1SMykiLCJ4MSI6NDU0My4wNDAwNjc4Mzk3OTYsInkxIjozNjMzLjAsIngyIjo1NjIxLjQ1OTU5Mjk2MTIyMiwieTIiOjQzMjUuMjk5OTk5OTk5OTk5LCJjb2xvciI6NDI4NTUwNzgwNCwiZGVzY3JpcHRpb24iOm51bGwsImNvbXBvbmVudElkcyI6Wy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
PROTOFLOW_REGION:eyJpZCI6ImE2OGJjMjA3LTU1ZmYtNDZkMC04NmZlLTA5OGI0YTBjYzZhZCIsIm5hbWUiOiJSZWdpc3RlciBGaWxlIChSMC1SMykiLCJ4MSI6NTQuMTQwMDAwMDAwMDAwMzMsInkxIjozNDUwLjExOTk5OTk5OTk5OSwieDIiOjQyODQuNjU5OTk5OTk5OTk5LCJ5MiI6NTQyMi41OCwiY29sb3IiOjQyODU1MDc4MDQsImRlc2NyaXB0aW9uIjpudWxsLCJjb21wb25lbnRJZHMiOl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
PROTOFLOW_REGION:eyJpZCI6IjE4NWYyMGNmLTUyYTgtNGM1Ny04NGU5LTA0Y2M4ZWY3MjE5YyIsIm5hbWUiOiJIYXJ2YXJkIE1lbW9yeSAoUk9NL1JBTSkiLCJ4MSI6NDg5OC4zOTU5OTk5OTk5OTksInkxIjo2OTUyLjc4LCJ4MiI6NTUzNC4wMjM5OTk5OTk5OTksInkyIjo3NTIwLjYyLCJjb2xvciI6NDI4NTUwNzgwNCwiZGVzY3JpcHRpb24iOm51bGwsImNvbXBvbmVudElkcyI6WyIxZjgxZD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
PROTOFLOW_REGION:eyJpZCI6ImY2OTY3NzNjLWM4YmYtNDVjZC1iZTc5LTdjMmRmNWUwYzFlNSIsIm5hbWUiOiJIYXJ2YXJkIE1lbW9yeSAoUk9NL1JBTSkiLCJ4MSI6Njc1NC40OTYwMDAwMDAwMDEsInkxIjo2OTg4LjMzOTk5OTk5OTk5OSwieDIiOjc0MjUuNjgzOTk5OTk5OTk5LCJ5MiI6NzQ4NS4wNiwiY29sb3IiOjQyODU1MDc4MDQsImRlc2NyaXB0aW9uIjpudWxsLCJjb21wb25lbnRJZH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
PROTOFLOW_REGION:eyJpZCI6ImFiNGUxNzU2LTkzOGMtNDU0MC05YmQwLWI2NzUyY2IxY2RjOSIsIm5hbWUiOiJBTFUgJiBBY2N1bXVsYXRvciIsIngxIjowLjAsInkxIjo0OTMuNTYwMDAwMDAwMDAwMDYsIngyIjo2ODgzLjk0LCJ5MiI6MTIwMy42NDAwMDAwMDAwMDAzLCJjb2xvciI6NDI4NTUwNzgwNCwiZGVzY3JpcHRpb24iOm51bGwsImNvbXBvbmVudElkcyI6WyIzMzY0MzM0Mi0zYjIzLT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
PROTOFLOW_REGION:eyJpZCI6Ijg2ODFlY2MxLTRjMzYtNGRlZC04YjliLWI3MTBjMTIyYTljNCIsIm5hbWUiOiJBTFUgJiBBY2N1bXVsYXRvciIsIngxIjo0MDIzLjg3OTI0NDI1MDMxOCwieTEiOjMwODIuMzA4NzM3MDgwMDA5NSwieDIiOjUyMjAuMDg2NzkyNjI0OTQ3LCJ5MiI6Mzk0Mi45NDg1NDM4MTk5OTcsImNvbG9yIjo0Mjg1NTA3ODA0LCJkZXNjcmlwdGlvbiI6bnVsbCwiY29tcG9uZW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
PROTOFLOW_REGION:eyJpZCI6IjVhOTA0ZGEzLTVlMGYtNDUyNS1hZDU1LTBmODg0NTQzZTlmYSIsIm5hbWUiOiJSZWdpc3RlciBGaWxlIChSMC1SMykiLCJ4MSI6MTA4NjIuNTYwMDY3ODM5Nzk1LCJ5MSI6Mzg0OS44NDAyNTQzOTkyMzYsIngyIjoxMTUzMi4wMzk1OTI5NjEyMTksInkyIjo0Mjg5LjE1OTk1NzYwMDEyNiwiY29sb3IiOjQyODU1MDc4MDQsImRlc2NyaXB0aW9uIjpudWxsLCJjb2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
PROTOFLOW_REGION:eyJpZCI6IjUzZDJhODUyLTQwOGItNDI2Yi1iODI4LTU2YmYwMDEwYTkwYSIsIm5hbWUiOiJQQyAmIE1BUiIsIngxIjoyODUwLjUzNTk5OTk5OTk5OSwieTEiOjU0OTcuMzYwMDAwMDAwMDAxLCJ4MiI6MzYwOC4zODQsInkyIjo1ODUxLjg0LCJjb2xvciI6NDI4NTUwNzgwNCwiZGVzY3JpcHRpb24iOm51bGwsImNvbXBvbmVudElkcyI6WyJkYzkwNTlmOS1kYWRlLTQ4YmEtOD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
PROTOFLOW_REGION:eyJpZCI6IjVmZGYwMzkxLTJiYTUtNGVlZS1iZWNjLTQxZjgwY2MxOGJiZiIsIm5hbWUiOiJBTFUgJiBBY2N1bXVsYXRvciIsIngxIjo1Nzg2LjA1OTk5OTk5OTk5OTUsInkxIjoxMjA3LjMsIngyIjo5MDYwLjI0LCJ5MiI6MzA1NS4yOTk5OTk5OTk5OTkzLCJjb2xvciI6NDI4NTUwNzgwNCwiZGVzY3JpcHRpb24iOm51bGwsImNvbXBvbmVudElkcyI6WyIzN2VmNzM1Yi1mNz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

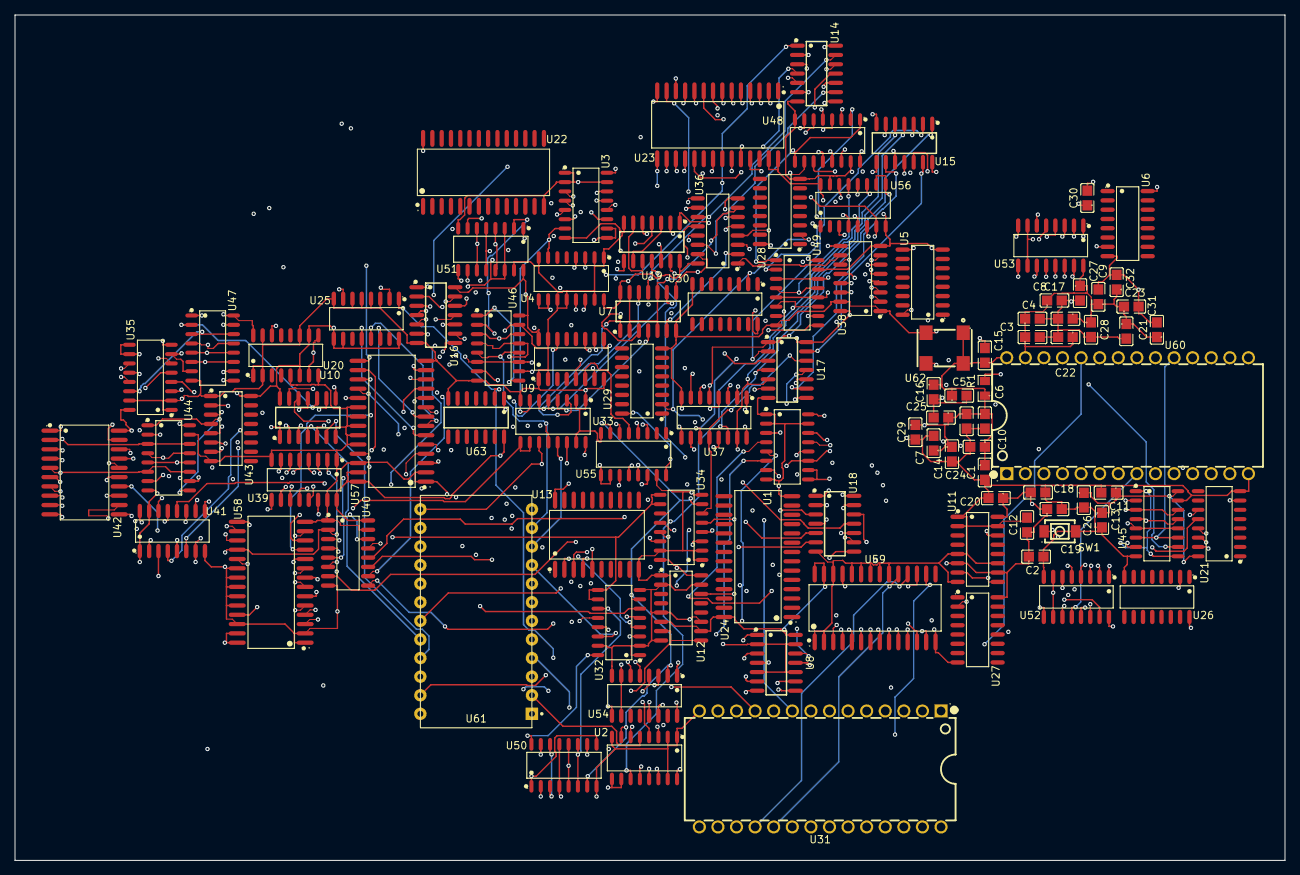
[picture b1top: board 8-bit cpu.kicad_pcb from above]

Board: 4 copper layers, 173.5 x 115.5 mm, 97 parts (0 on the bottom side), 178 nets.
